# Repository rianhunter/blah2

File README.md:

# A ADA4857 dual channel amplifier for VHS decode RF capture

An [ADA4857][ada4857-datasheet] based, configurable, dual channel amplifier and line driver for [VHS decode][vhs-decode].
The board is intended to be permanently mounted into a chosen VHS player, providing an amplified, 75 Ohms impedance output for the video and HiFi audio RF signals.
Find gerbers, BOM and pick'n'place files ready for fabrication over in the [releases section](https://gitlab.com/wolfre/vhs-rf-amp-ada4857/-/releases).
Most of the boards are pre-assembled, but you will need to choose (and solder) the appropriate components fitting for your VHS player for final installation.

This project is a follow up / improvement on the [previous SGM8302 dual channel amplifier](https://gitlab.com/wolfre/vhs-rf-amp-sgm8302) of the same nature.

## Overview

The following diagram shows the intended usecase for this dual channel amplifier installed into a VHS player.
The Parts that are coming from this project and will be installed are drawn in blue.

The design is based on two [ADA4857][ada4857-datasheet] single channel op amps, with a [DS8604-A0S3][ds8604-datasheet] 10V LDO and a few other passive components.
Both RF paths are identical and all the following discussion applies to path A and B equally.
The op amps are driven from a single 10V power supply (via an [LDO][wiki-ldo]), meaning the neutral / center voltage for the op amps is 5V.
Each of the amp inputs is being AC coupled into a termination resistor (a 1:1 divider to add the needed 5V DC offset) and will need to be configured according to your VHS players needs (see [build guide][self-build-guide]).
The op amps are used in a non-inverting design with a fixed gain factor, which also must be configured according to your VHS players signals (see [build guide][self-build-guide]).
The amp outputs have a DC block capacitor and 75 Ohms resistor in series, for the usual 75 Ohms impedance line and load to drive.
Mechanically the board is designed for [edge mount SMA connectors](https://www.google.com/search?q=sma+connector+edge+mount) but can also fit 2.54mm pin headers mounted sideways, or direct soldering.

## Build guide

This amp is intended to permanently mount into one specific VHS player and *adapt* the tape head amps RF signals to 75 Ohm lines / systems.
Each player is electrically different and so you will need to select a couple of components to match the amp board to your model.
The following guide will walk you through each step in details.
Before you start ordering and building, you should read the entire guide at least once so you know what to expect.
Here's an overview of the steps you will needed to do:
- [Order the amp boards with JLCPCB][ordering-guide-jlc] (most of the components come pre-assembled from the fab).
- Install a tap on the RF video and RF HiFi signals from the tape head amp of your player.
  As this is specific to your player model, only some general information is covered in this guide.
- Find a suitable power supply rail in your VHS player (something with at least 12V).
  And configure the amp boards power supply section to work with your chosen power rail.
- Configure each amp paths input termination to match / work with the players head amps.
- Configure each amp paths signal gain to deliver a signal level high enough to fit your capture device.
- Mount the amp board into your VHS player and wire up suitable output connectors.
  As this is specific to your player model, this step is beyond the scope of this guide and will not be covered.

The adaption of the power supply, input termination and gain factors will require soldering.
Don't worry though all parts are either rather large 0805 SMD parts, or through hole.
If you are new to soldering electronics, learning about it is a bit beyond this guide.
However you may want to start looking here, as these videos cover the things needed for this guide:
- Branchus Creations Beginner's Guide to Soldering Electronics [Part 1](https://www.youtube.com/watch?v=M2Jf8cebwCs) and [Part 2](https://www.youtube.com/watch?v=BPuH1Z2npoQ)
- Electronoobs [SMD Soldering Tutorial | Guide | Tools | Tecniques | Stencil](https://www.youtube.com/watch?v=fYInlAmPnGo)

Also you will be dealing with high frequency analog signals, that need to be measured and observed to find the correct input termination and gain factor.
This requires either a [Digital storage oscilloscope][wiki-dso], or an [analog oscilloscope][wiki-scope] in good working order.
To correctly assess the signals, your scope should have an analog bandwidth of at least 20MHz, and you need high impedance probes as well
(1M or greater, usually the 10x setting on your oscilloscopes probes is a good fit).
This guide will assume you are familiar with oscilloscopes (you may have have a look at GreatScott!s [Everything you need to know when buying/using an Oscilloscope! EB#49](https://www.youtube.com/watch?v=d58GzhXKKG8) to get started).

As evident from the steps above, you will need to know your way around your VHS player and a service manual will be of great help.

### Ordering the PCBs and additional components

The PCBs can currently be ordered from JLC, and come mostly pre-assembled.
See the [ordering guide over here][ordering-guide-jlc] for details on the ordering process.
The board is missing a few components that are specific to your VHS player.
Selecting them will be covered in subsequent sections, but here's a list of what you need (buy) in addition to the PCBs:
- 4x edge mount SMA connectors, with about 6.5mm edge length and about 1.6mm PCB thickness.
  Alternatively 4x 2.54mm pin headers with 3 connectors.
- Coax cable for taping the RF signals and bringing them to the amp board.
  Those cables are probably fitted with SMA connectors on one end, matching the edge mount SMA connector on the amp board.
- Additional (75 Ohms) coax cabling to bring the signal from the amp board to some connector accessible on the outside of your VHS player.
  The outside facing connector is most likely BNC, as 75 Ohms cables are readily available for these.
  The inside facing end will probably have a matching SMA connector to mate with the amp board outputs.
- Depending on your power supply situation inside the VHS player, a Zener diode is needed.
  See [power supply section][self-pwr] later on for details.
- A set of 0805 resistors to configure the input termination and gain setting on each amp path.
  See the [Adapting the amp inputs to your VHS player][self-adapt-input] and [Adapting the amp gain to your VHS player][self-adapt-gain] sections for details.
  However a common [0805 E24 resistor set with 1% tolerance][ebay-0805-r] is probably the cheapest option and should cover your needs.
- Generic insulated wire to supply power to the amp board.
  Optionally you can install pin header on the amp board instead of soldering the power supply directly.
- Anything needed to fixate / mount the amp board into your VHS player (e.g. M3 screws / nuts).
- Usual consumables like solder, heat shrink tubing etc.

### RF tap

The [VHS-Decode wiki][rf-tap] has an ever growing wealth of information on various players, so you should start over there.

When looking for an RF tap point, the goal is to be as close to the tape head amplifier outputs as possible.
The following diagram shows the logical components of a VHS RF tape pickup inside your player (both the RF video and HiFi RF audio paths will look similar).

The ideal tap point is right after the head switch, so that one RF signal contains both head outputs.
The newer your player the more components will be integrated in to complex ICs and may not be available separately.
Also there may be an additional set of video heads that is used for EP playback.

Look for your video and audio tap points and solder a well shielded coax cable to each one.
You don't need to add a DC block capacitor, as those are included on the amp boards.

### Power supply section

The board features an [DS8604-A0S3][ds8604-datasheet] LDO that supplies 10V to the two ADA4857 amps.
The input voltage can be from around 11V to 55V according to the data sheet.
However as any voltage dropped on the [LDO][wiki-ldo] is dissipated as heat, the higher the input voltage the hotter the IC will get.
To keep the temperature of the IC down to a reasonable level, the LDO input voltage should not exceed 20V.
A very common voltage to find in VHS player power supplies is 12V, which is an optimal fit.
If that is not available to you, higher voltages like 30V are also a common sight.
To make the board work with such higher voltages, a [Zener diode][wiki-zener] can be installed to drop the addition voltage.
When looking for a ground to power the board, make sure to double check that this is the same ground as the one from your head amp signal (multimeter reads 0 Ohm between the two grounds).

The above image shows the voltage input pins of connector J1 on the left.
This is where you connect the full input voltage from the VHS players power supply rail.
On the right C1 is visible, which is the input buffer capacitor before the LDO.
In the middle you can see the location for the optional [Zener diode][wiki-zener].

The total current draw of both [ADA4857][ada4857-datasheet] amps should be around 50mA.
So keep in mind that the [Zener diode][wiki-zener] you select must be able to dissipate the dropped voltage as heat.
The following table gives a quick overview on the selection of the diode, based on available input voltage.

| Vin (from PSU) | [Zener diode][wiki-zener] voltage rating | [Zener diode][wiki-zener] power rating |
|----------------|------------------------------------------|----------------------------------------|
| 12V            | no diode needed, short connections       |                                        |
| 20V            | 6~7 V diode recommended but not required | at least 0.5 W                         |
| 30V            | 10~15 V diode required                   | at least 1 W                           |
| 40V            | 20~25 V diode required                   | at least 2 W                           |

[Zener diodes][wiki-zener] are available with higher voltages, but this means ever more heat dissipation.
Instead you can also add an additional DC/DC step-down converter, that more efficiently produces the optimal 12V.
The [XL4015][xl4015-datasheet] IC is a good fit and can take up to 36V on its inputs.
Finished boards are cheaply and readily available on [ebay][ebay-xl4015] or other places.
These do however operate on a high frequency switching design (around 100~200kHz for the [XL4015][xl4015-datasheet]) and may introduce noise on the signal paths.
So you may want to think about shielding such a DC/DC converter.
You can take inspiration from the shielding of the PSU inside your VHS player as those usually are switch mode designs, that equally produce RF interference.

### Adapting the amp inputs to your VHS player

The inputs are AC coupled via C11 + R11 + R12 and C21 + R21 + R22.
Both caps are pre populated as 10µF, which should be good for any VHS player setup.
The resistors however are not populated from the factory, and need to be selected to work with the tape head amp output on [your RF tap][rf-tap].
Here's a rough guide on how to do this with some try'n'error (having a common resistor set at hand is a good idea).

Take a look at the service manual (if you have it), and look for resistors around the signal path you tapped.
Choose a value that is around 10x higher than the values you observe (e.g. 1.5k is around the signal path, go for a 15k Ohms resistor), but to be safe *don't go below 1k Ohms*.
If you don't have the service manual you can just start with about 100k Ohms.

Hook up a [DSO][wiki-dso] to the output of your tap and observe the signal levels.
Temporarily attach the chosen resistor value between signal and (analog) ground to see if the levels drop.
If they stay the same then repeat with a resistor value that is about half your current value, if they do drop, double the value.
You are looking for a value where the signal is just barely dropping, multiply that value by 20, that's your input termination.
This termination value is then installed in both R11 and R12 positions (or R21 and R22 respectively).

One of the signal paths is going to be for video, the other for audio.
As both path A and B are equal on the [ADA4857][ada4857-datasheet] amp board, it does not matter which path is used for what signal.
But you have to do the above try'n'error sequence for both head amps / taps as they possibly differ.

### Adapting the amp gain to your VHS player

Once you have your input stage setup, you need to choose the gain for each signal path.
To do that, observe the video and audio RF signal levels from your tap points when playing different VHS tapes.
Different tapes will have different signal levels (test newer and older tapes, NTSC and PAL, etc).
Consulting the service manual for your player may also give you a good idea about the expected signal levels.
Based on this you now need to choose the values for R13 + R14 (path A) and R23 + R24 (path B).
Again every VHS player is different, but just for reference, the video levels could be somewhere around 100mVpp to 300mVpp.
HiFi RF signal levels are usually higher than video levels, so maybe 500mVpp ~ 1000mVpp.

You should also know what your target capture device needs as a good input range.
A [CXADC](https://github.com/happycube/cxadc-linux3) seems to be [fine with about 1.5Vpp](https://gitlab.com/wolfre/cx25800-11z-cxadc-rework-measurements) (peak-to-peak).

So lets say you observe 0.5Vpp (500mVpp) of signal level and your device is a CX based capture card, so a target of 1.5Vpp.
This means we need 6x gain, here's why: from 0.5V to 1.5V is a 3x gain, but you also need to have [2x for the transmission line](https://electronics.stackexchange.com/questions/550000/50-ohms-output-termination-for-a-50ohms-load), 2 x 3 gives a gain of 6.
The following tables lists good combinations for the resistor pairs from the [E12](https://en.wikipedia.org/wiki/E_series_of_preferred_numbers) series.
In doubt select the next lower gain to get more headroom on the ADC input.

|Rf (Ohms) | Rin (Ohms) | gain | Est. upper -3dB bandwidth (MHz)| Est. lower -3dB bandwidth (Hz) |
|----------|------------|------|--------------------------------|--------------------------------|
| 560      | 1000       |  1.6 | 500                            | 22                             |
| 560      | 560        |  2.0 | 350                            | 22                             |
| 560      | 270        |  3.0 | 180                            | 22                             |
| 560      | 180        |  4.1 | 120                            | 22                             |
| 560      | 150        |  4.7 |  95                            | 22                             |
| 560      | 120        |  5.6 |  75                            | 28                             |
| 560      | 100        |  6.6 |  60                            | 33                             |
| 560      |  82        |  7.8 |  55                            | 41                             |
| 560      |  68        |  9.2 |  45                            | 50                             |
| 560      |  56        | 11.0 |  35                            | 60                             |
| 560      |  47        | 12.9 |  30                            | 72                             |
| 560      |  39        | 15.4 |  25                            | 87                             |

The upper bandwidth estimations are based on an extrapolation for the couple values from the data sheet.
They are only rough guidelines and don't take into account anything but the amp IC.
So no tap point quality, PCB design, connector losses, cabling limits, etc.
The lower bandwidth estimations are based on the high pass filter of the Rin with the 47uF DC blocking capacitor.
For lower gain settings, the lower bandwidth is further limited by the 150 Ohms output load and the 47 uF DC blocking capacitor.

The above table lists Rf and Rin values, the mapping is as follows:
- Path A
  - Rf = R14
  - Rin = R13
- Path B
  - Rf = R24
  - Rin = R23

As mentioned previously the design of the board fits a 75 Ohms impedance / transmission line and termination.
This is the default found on CX based capture cards and in other video based applications.
However R15 and/or R24 can be changed to 50 Ohms:
- by replacing the resistors with a 50 Ohms 0603 by editing the BOM when ordering
- after ordering by de-soldering the 75 Ohms and replacing them with 50 Ohms
- by soldering a 150 Ohms 0603 in parallel to a 75 Ohms

## Changelog

See [CHANGELOG.md](CHANGELOG.md).

## Releases

See [releases](https://gitlab.com/wolfre/vhs-rf-amp-ada4857/-/releases) for PCB gerbers, BOM and pick'n'place files ready for fabrication.

## License

See [LICENSE.md](LICENSE.md)

[ada4857-datasheet]: https://www.analog.com/media/en/technical-documentation/data-sheets/ADA4857-1_4857-2.pdf
[ds8604-datasheet]: https://jlcpcb.com/partdetail/Dstech-DS8604A0S3/C5884205
[self-build-guide]: #build-guide
[self-pwr]: #power-supply-section
[self-adapt-input]: #adapting-the-amp-inputs-to-your-vhs-player
[self-adapt-gain]: #adapting-the-amp-gain-to-your-vhs-player
[ordering-guide-jlc]: order-jlc/ordering-guide.md
[wiki-dso]: https://en.wikipedia.org/wiki/Digital_storage_oscilloscope
[wiki-scope]: https://en.wikipedia.org/wiki/Oscilloscope
[rf-tap]: https://github.com/oyvindln/vhs-decode/wiki/Hardware-Installation-Guide
[wiki-zener]: https://en.wikipedia.org/wiki/Zener_diode
[ebay-0805-r]: https://www.ebay.com/sch/i.html?_nkw=0805+smd+resistor+kit
[ebay-xl4015]: https://www.ebay.com/sch/i.html?&_nkw=XL4015+step+down
[wiki-ldo]: https://en.wikipedia.org/wiki/Low-dropout_regulator
[xl4015-datasheet]: https://datasheet.lcsc.com/lcsc/1811081616_XLSEMI-XL4015E1_C51661.pdf
[vhs-decode]: https://github.com/oyvindln/vhs-decode

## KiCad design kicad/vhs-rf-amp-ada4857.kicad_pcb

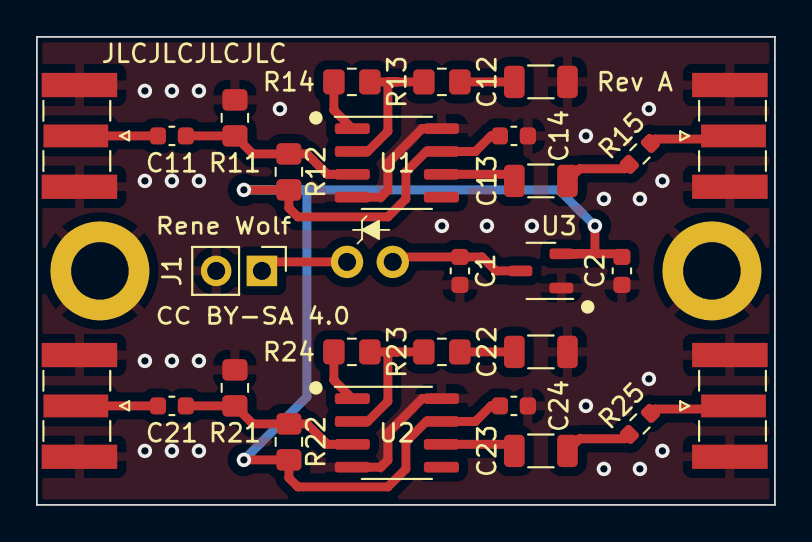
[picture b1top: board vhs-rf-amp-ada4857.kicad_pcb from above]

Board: 2 copper layers, 41.0 x 26.0 mm, 31 parts (0 on the bottom side), 20 nets.

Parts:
C1, C2, C11, C21: 10uf; C_0603_1608Metric
C12, C13, C22, C23: 47uf; C_1206_3216Metric
C14, C24: 100nf; C_0603_1608Metric
H1, H2: MountingHole_Pad; MountingHole_3.2mm_M3_ISO14580_Pad
J1: Conn_01x02_Pin; PinHeader_1x02_P2.54mm_Vertical
J2: Conn_01x02_Pin; zener_THT_P2.54mm
J11, J12, J21, J22: Conn_Coaxial; SMA_Samtec_SMA-J-P-X-ST-EM1_EdgeMount
R11, R12, R13, R14, R21, R22, R23, R24: 50k; R_0805_2012Metric_Pad1.20x1.40mm_HandSolder
R15, R25: 75; R_0603_1608Metric
U1, U2: ADA4857-1YRZ; SOIC-8_3.9x4.9mm_P1.27mm
U3: DS8604-A0S3; SOT-23-3

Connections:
/vss: C2.1, C14.1, C24.1, R12.1, R22.1, U1.7 (+Vs), U2.7 (+Vs), U3.2 (VOUT)
GND: C1.2, C2.2, C12.2, C14.2, C22.2, C24.2, H1.1, H2.1, J1.2, J11.2 (Ext), J12.2 (Ext), J21.2 (Ext), J22.2 (Ext), R11.2, R21.2, U1.4 (-Vs), U1.8 (PD), U2.4 (-Vs), U2.8 (PD), U3.1 (GND)
unnamed: C12.1, R13.1
unnamed: C13.1, R15.1
unnamed: C22.1, R23.1
unnamed: C23.1, R25.1
unnamed: J1.1, J2.1
unnamed: C1.1, J2.2, U3.3 (VIN)
unnamed: C11.1, J11.1 (In)
unnamed: J12.1 (In), R15.2
unnamed: C21.1, J21.1 (In)
unnamed: J22.1 (In), R25.2
unnamed: C11.2, R11.1, R12.2, U1.3 (+IN)
unnamed: R13.2, R14.1, U1.2 (-IN)
unnamed: R14.2, U1.1 (FB)
unnamed: C13.2, U1.6 (OUT)
unnamed: C21.2, R21.1, R22.2, U2.3 (+IN)
unnamed: R23.2, R24.1, U2.2 (-IN)
unnamed: R24.2, U2.1 (FB)
unnamed: C23.2, U2.6 (OUT)

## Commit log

2024-01-04 throw in initial files
2024-01-05 more work on inital design
2024-01-05 more work on doc details
2024-01-05 more details
2024-01-05 bump changelog
2024-01-07 Resolve "A few minor doc updates"

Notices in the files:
README.md:
License:
See [LICENSE.md](LICENSE.md)
[ordering-guide-jlc]: order-jlc/ordering-guide.md
[rf-tap]: h
kicad/vhs-rf-amp-ada4857.kicad_pcb:
CC BY-SA 4.0
